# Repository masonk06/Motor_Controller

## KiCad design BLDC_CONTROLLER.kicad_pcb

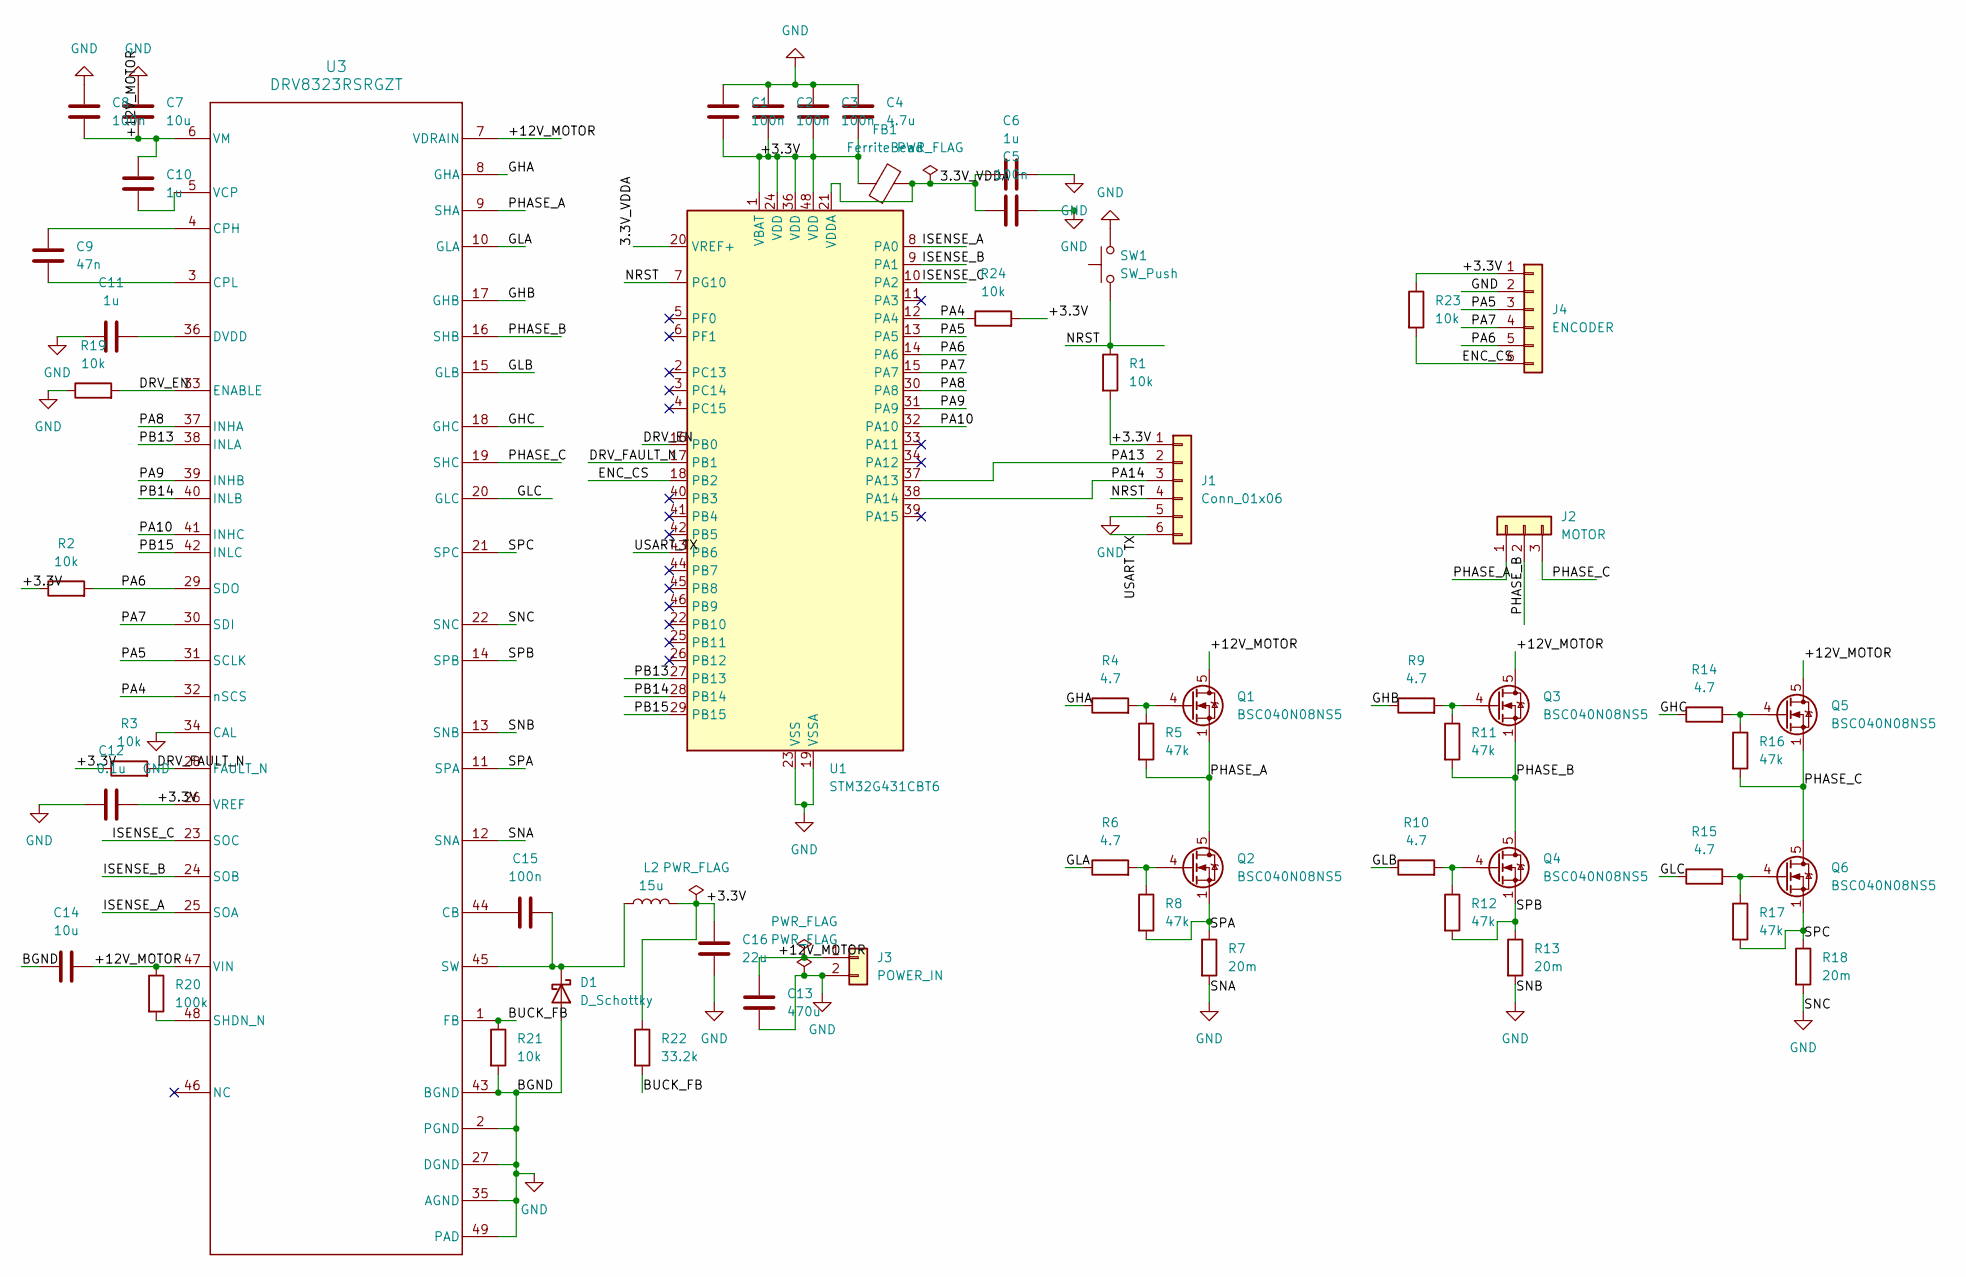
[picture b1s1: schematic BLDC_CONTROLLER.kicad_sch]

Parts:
C1, C2, C3, C5, C15: 100n; C_0805_2012Metric
C4: 4.7u; C_0805_2012Metric
C6, C11: 1u; C_0805_2012Metric
C7, C14: 10u; C_1210_3225Metric
C8: 100n; C_0805_2012Metric; Voltage 50
C9: 47n; C_0805_2012Metric
C10: 1u; C_0805_2012Metric; Voltage 25V
C12: 0.1u; C_0805_2012Metric
C13: 470u; CP_Radial_D10.0mm_P5.00mm
C16: 22u; C_1206_3216Metric
D1: D_Schottky; D_SMA
FB1: FerriteBead; L_0805_2012Metric
J1: Conn_01x06; PinHeader_1x06_P2.54mm_Vertical
J2: MOTOR; TerminalBlock_Phoenix_MKDS-3-3-5.08_1x03_P5.08mm_Horizontal
J3: POWER_IN; AMASS_XT60-F_1x02_P7.20mm_Vertical
J4: ENCODER; PinHeader_1x06_P2.54mm_Vertical
L2: 15u; L_Coilcraft_XAL6060-XXX
Q1, Q2, Q3, Q4, Q5, Q6: BSC040N08NS5; TDSON-8-1
R1, R2, R3, R19, R21, R23, R24: 10k; R_0805_2012Metric
R4, R6, R9, R10, R14, R15: 4.7; R_0805_2012Metric
R5, R8, R11, R12, R16, R17: 47k; R_0805_2012Metric
R7, R13, R18: 20m; R_1206_3216Metric
R20: 100k; R_0805_2012Metric
R22: 33.2k; R_0805_2012Metric
SW1: SW_Push; SW_PUSH_6mm
U1: STM32G431CBT6; LQFP-48_7x7mm_P0.5mm; MPN STM32G431CBT6
U3: DRV8323RSRGZT; RGZ0048A_GND

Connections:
/3.3V_VDDA: C5.1, C6.1, FB1.2, U1.20 (VREF+), U1.21 (VDDA)
/+3.3V: C1.2, C2.2, C3.2, C4.2, C12.2, C16.1, FB1.1, J1.1, J4.1, L2.2, R1.2, R2.1, R3.1, R22.1, R23.1, R24.2, U1.1 (VBAT), U1.24 (VDD), U1.36 (VDD), U1.48 (VDD), U3.26 (VREF)
/+12V_MOTOR: C7.2, C8.2, C10.1, C13.1, C14.2, J3.1, Q1.5 (D), Q3.5 (D), Q5.5 (D), R20.1, U3.6 (VM), U3.7 (VDRAIN), U3.47 (VIN)
/BUCK_FB: R21.1, R22.2, U3.1 (FB)
/DRV_EN: R19.2, U1.16 (PB0), U3.33 (ENABLE)
/DRV_FAULT_N: R3.2, U1.17 (PB1), U3.28 (FAULT_N)
/ENC_CS: J4.6, R23.2, U1.18 (PB2)
/GHA: R4.1, U3.8 (GHA)
/GHB: R9.1, U3.17 (GHB)
/GHC: R14.1, U3.18 (GHC)
/GLA: R6.1, U3.10 (GLA)
/GLB: R10.1, U3.15 (GLB)
/GLC: R15.1, U3.20 (GLC)
/ISENSE_A: U1.8 (PA0), U3.25 (SOA)
/ISENSE_B: U1.9 (PA1), U3.24 (SOB)
/ISENSE_C: U1.10 (PA2), U3.23 (SOC)
/NRST: J1.4, R1.1, SW1.1, U1.7 (PG10)
/PA4: R24.1, U1.12 (PA4), U3.32 (nSCS)
/PA5: J4.3, U1.13 (PA5), U3.31 (SCLK)
/PA6: J4.5, R2.2, U1.14 (PA6), U3.29 (SDO)
/PA7: J4.4, U1.15 (PA7), U3.30 (SDI)
/PA8: U1.30 (PA8), U3.37 (INHA)
/PA9: U1.31 (PA9), U3.39 (INHB)
/PA10: U1.32 (PA10), U3.41 (INHC)
/PA13: J1.2, U1.37 (PA13)
/PA14: J1.3, U1.38 (PA14)
/PB13: U1.27 (PB13), U3.38 (INLA)
/PB14: U1.28 (PB14), U3.40 (INLB)
/PB15: U1.29 (PB15), U3.42 (INLC)
/PHASE_A: J2.1, Q1.1 (S), Q1.2 (S), Q1.3 (S), Q2.5 (D), R5.2, U3.9 (SHA)
/PHASE_B: J2.2, Q3.1 (S), Q3.2 (S), Q3.3 (S), Q4.5 (D), R11.2, U3.16 (SHB)
/PHASE_C: J2.3, Q5.1 (S), Q5.2 (S), Q5.3 (S), Q6.5 (D), R16.2, U3.19 (SHC)
/SPA: Q2.1 (S), Q2.2 (S), Q2.3 (S), R7.1, R8.2, U3.11 (SPA)
/SPB: Q4.1 (S), Q4.2 (S), Q4.3 (S), R12.2, R13.1, U3.14 (SPB)
/SPC: Q6.1 (S), Q6.2 (S), Q6.3 (S), R17.2, R18.1, U3.21 (SPC)
/USART TX: J1.6
/USART_TX: U1.43 (PB6)
GND: C1.1, C2.1, C3.1, C4.1, C5.2, C6.2, C7.1, C8.1, C11.1, C12.1, C13.2, C14.1, C16.2, D1.2 (A), J1.5, J3.2, J4.2, R7.2, R13.2, R18.2, R19.1, R21.2, SW1.2, U1.19 (VSSA), U1.23 (VSS), U1.35 (VSS), U1.47 (VSS), U3.2 (PGND), U3.12 (SNA), U3.13 (SNB), U3.22 (SNC), U3.27 (DGND), U3.34 (CAL), U3.35 (AGND), U3.43 (BGND), U3.49 (PAD)
unnamed: C15.2, D1.1 (K), L2.1, U3.45 (SW)
unnamed: Q1.4 (G), R4.2, R5.1
unnamed: Q2.4 (G), R6.2, R8.1
unnamed: Q3.4 (G), R9.2, R11.1
unnamed: Q4.4 (G), R10.2, R12.1
unnamed: Q5.4 (G), R14.2, R16.1
unnamed: Q6.4 (G), R15.2, R17.1
unnamed: C15.1, U3.44 (CB)
unnamed: C9.1, U3.4 (CPH)
unnamed: C9.2, U3.3 (CPL)
unnamed: C11.2, U3.36 (DVDD)
unnamed: R20.2, U3.48 (SHDN_N)
unnamed: C10.2, U3.5 (VCP)

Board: 2 copper layers, 56 parts (0 on the bottom side), 49 nets, no tracks yet.
